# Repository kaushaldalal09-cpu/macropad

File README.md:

# macropad

This macropad will serve three purposes. One is to increase efficiency for my work by opening my most used apps with the click of a button. The second purpose is for playing video games. And the third feature I want is to have a built in game of tetris using the keys and oled display. My macro pad will include a knob (which will increase/decrease the volume) , a oled screen (to show the volume, or the tetris game depending on what mode I'm in), 12 keys, and RGB lights. 

All silkscreen artwork was created by me

BOM:
|Reference                                      |Qty|Value               |DNP|Exclude from BOM |Exclude from Board|Footprint                                                     |Datasheet                                                                 |
|-----------------------------------------------|---|--------------------|---|-----------------|------------------|--------------------------------------------------------------|--------------------------------------------------------------------------|
|C1                                             |1  |1.0uF               |   |                 |                  |Capacitor_THT:C_Axial_L5.1mm_D3.1mm_P15.00mm_Horizontal       |~                                                                         |
|D1,D2,D3,D4,D5,D6,D7,D8,D9                     |9  |1N4148              |   |                 |                  |Diode_THT:D_DO-35_SOD27_P7.62mm_Horizontal                    |https://assets.nexperia.com/documents/data-sheet/1N4148_1N4448.pdf        |
|D10,D11,D12,D13,D14,D15,D16,D17,D18,D19,D20,D21|12 |SK6812MINI          |   |                 |                  |LED_SMD:LED_SK6812MINI_PLCC4_3.5x3.5mm_P1.75mm                |https://cdn-shop.adafruit.com/product-files/2686/SK6812MINI_REV.01-1-2.pdf|
|H1,H2,H3,H4                                    |4  |MountingHole        |   |Excluded from BOM|                  |MountingHole:MountingHole_3.2mm_M3                            |~                                                                         |
|J1                                             |1  |Conn_01x04_Pin      |   |                 |                  |Connector_PinHeader_2.54mm:PinHeader_1x04_P2.54mm_Vertical    |~                                                                         |
|R1,R2                                          |2  |4.7K                |   |                 |                  |Resistor_THT:R_Axial_DIN0207_L6.3mm_D2.5mm_P10.16mm_Horizontal|~                                                                         |
|SW1,SW2,SW3,SW4,SW5,SW6,SW7,SW8                |8  |SW_Push             |   |                 |                  |Button_Switch_Keyboard:SW_Cherry_MX_1.00u_PCB                 |~                                                                         |
|SW9                                            |1  |RotaryEncoder_Switch|   |                 |                  |Rotary_Encoder:RotaryEncoder_Alps_EC11E-Switch_Vertical_H20mm |~                                                                         |
|U1                                             |1  |XIAO-RP2040-DIP     |   |                 |                  |OPL Lib:XIAO-RP2040-DIP                                       |                                                                          |

Resources used:

https://www.thingiverse.com/thing:6940808

https://github.com/ConstantinoSchillebeeckx/cherry-mx-switch/blob/master/switch.step

https://github.com/ConstantinoSchillebeeckx/cherry-mx-keycaps/blob/master/STEP/Cherry%20MX%20keycaps.step

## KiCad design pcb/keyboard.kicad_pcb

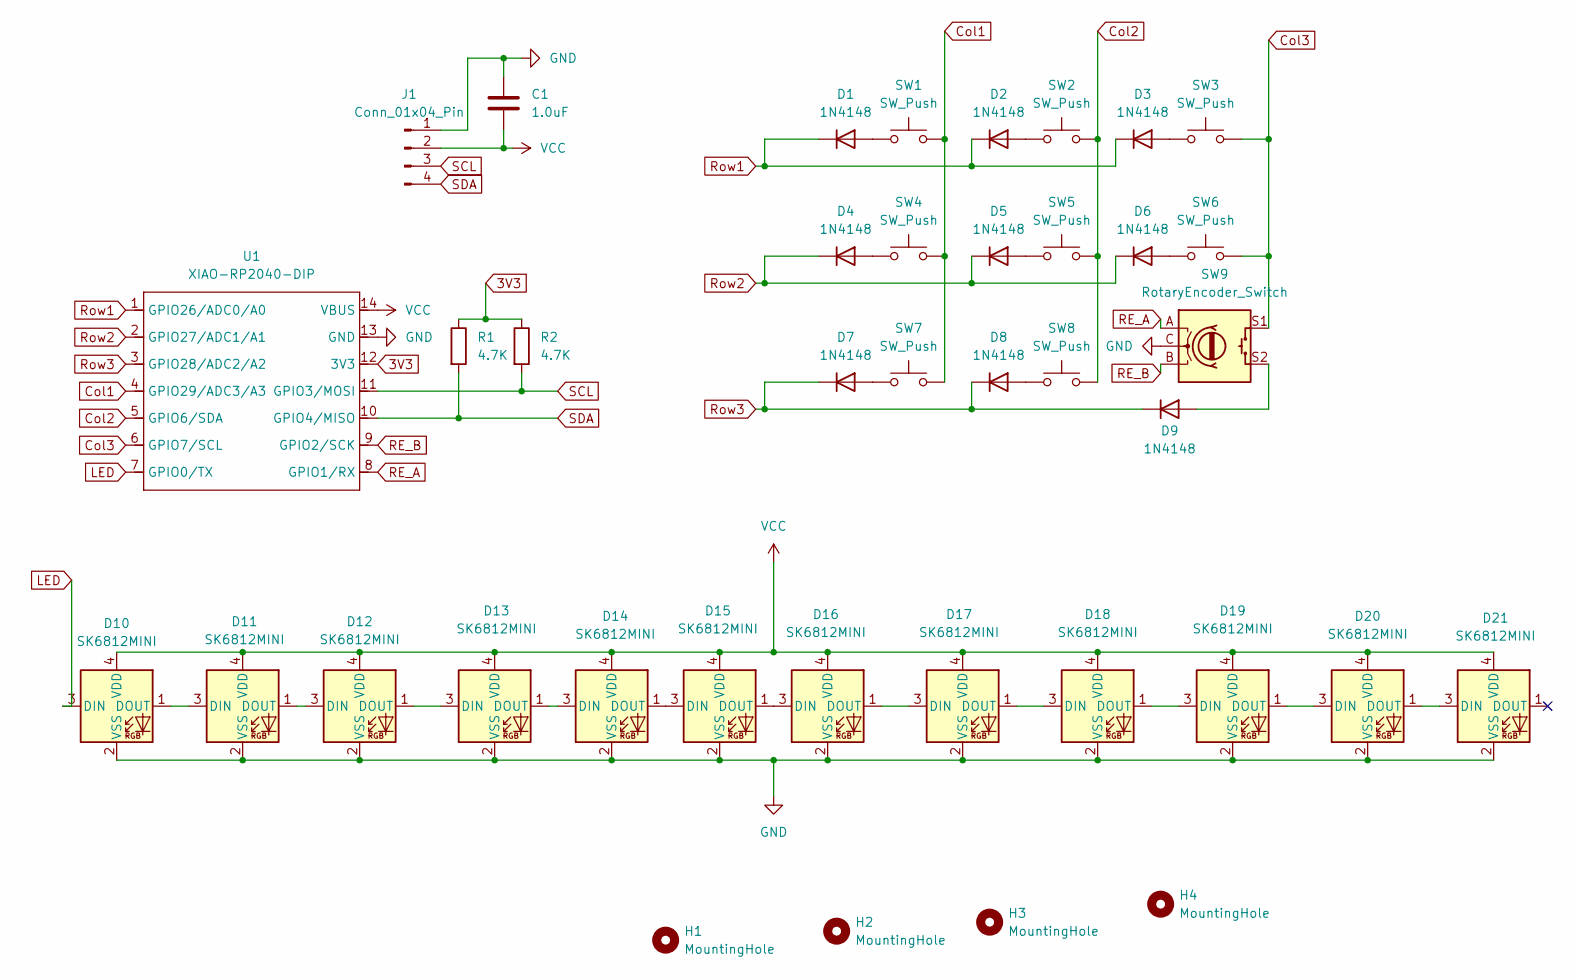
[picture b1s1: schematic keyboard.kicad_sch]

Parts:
C1: 1.0uF; C_Axial_L5.1mm_D3.1mm_P15.00mm_Horizontal
D1, D2, D3, D4, D5, D6, D7, D8, D9: 1N4148; D_DO-35_SOD27_P7.62mm_Horizontal
D10, D11, D12, D13, D14, D15, D16, D17, D18, D19, D20, D21: SK6812MINI; LED_SK6812MINI_PLCC4_3.5x3.5mm_P1.75mm
H1, H2, H3, H4: MountingHole; MountingHole_3.2mm_M3
J1: Conn_01x04_Pin; PinHeader_1x04_P2.54mm_Vertical
R1, R2: 4.7K; R_Axial_DIN0207_L6.3mm_D2.5mm_P10.16mm_Horizontal
SW1, SW2, SW3, SW4, SW5, SW6, SW7, SW8: SW_Push; SW_Cherry_MX_1.00u_PCB
SW9: RotaryEncoder_Switch; RotaryEncoder_Alps_EC11E-Switch_Vertical_H20mm
U1: XIAO-RP2040-DIP

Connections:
3V3: R1.1, R2.1, U1.12 (3V3)
Col1: SW1.2, SW4.2, SW7.2, U1.4 (GPIO29/ADC3/A3)
Col2: SW2.2, SW5.2, SW8.2, U1.5 (GPIO6/SDA)
Col3: SW3.2, SW6.2, SW9.S1, U1.6 (GPIO7/SCL)
GND: C1.1, D10.2 (VSS), D11.2 (VSS), D12.2 (VSS), D13.2 (VSS), D14.2 (VSS), D15.2 (VSS), D16.2 (VSS), D17.2 (VSS), D18.2 (VSS), D19.2 (VSS), D20.2 (VSS), D21.2 (VSS), J1.1, SW9.C, U1.13 (GND)
LED: D10.3 (DIN), U1.7 (GPIO0/TX)
unnamed: D1.2 (A), SW1.1
unnamed: D2.2 (A), SW2.1
unnamed: D3.2 (A), SW3.1
unnamed: D4.2 (A), SW4.1
unnamed: D5.2 (A), SW5.1
unnamed: D6.2 (A), SW6.1
unnamed: D7.2 (A), SW7.1
unnamed: D8.2 (A), SW8.1
unnamed: D9.2 (A), SW9.S2
unnamed: D10.1 (DOUT), D11.3 (DIN)
unnamed: D11.1 (DOUT), D12.3 (DIN)
unnamed: D12.1 (DOUT), D13.3 (DIN)
unnamed: D13.1 (DOUT), D14.3 (DIN)
unnamed: D14.1 (DOUT), D15.3 (DIN)
unnamed: D15.1 (DOUT), D16.3 (DIN)
unnamed: D16.1 (DOUT), D17.3 (DIN)
unnamed: D17.1 (DOUT), D18.3 (DIN)
unnamed: D18.1 (DOUT), D19.3 (DIN)
unnamed: D19.1 (DOUT), D20.3 (DIN)
unnamed: D20.1 (DOUT), D21.3 (DIN)
RE_A: SW9.A, U1.8 (GPIO1/RX)
RE_B: SW9.B, U1.9 (GPIO2/SCK)
Row1: D1.1 (K), D2.1 (K), D3.1 (K), U1.1 (GPIO26/ADC0/A0)
Row2: D4.1 (K), D5.1 (K), D6.1 (K), U1.2 (GPIO27/ADC1/A1)
Row3: D7.1 (K), D8.1 (K), D9.1 (K), U1.3 (GPIO28/ADC2/A2)
SCL: J1.3, R2.2, U1.11 (GPIO3/MOSI)
SDA: J1.4, R1.2, U1.10 (GPIO4/MISO)
VCC: C1.2, D10.4 (VDD), D11.4 (VDD), D12.4 (VDD), D13.4 (VDD), D14.4 (VDD), D15.4 (VDD), D16.4 (VDD), D17.4 (VDD), D18.4 (VDD), D19.4 (VDD), D20.4 (VDD), D21.4 (VDD), J1.2, U1.14 (VBUS)

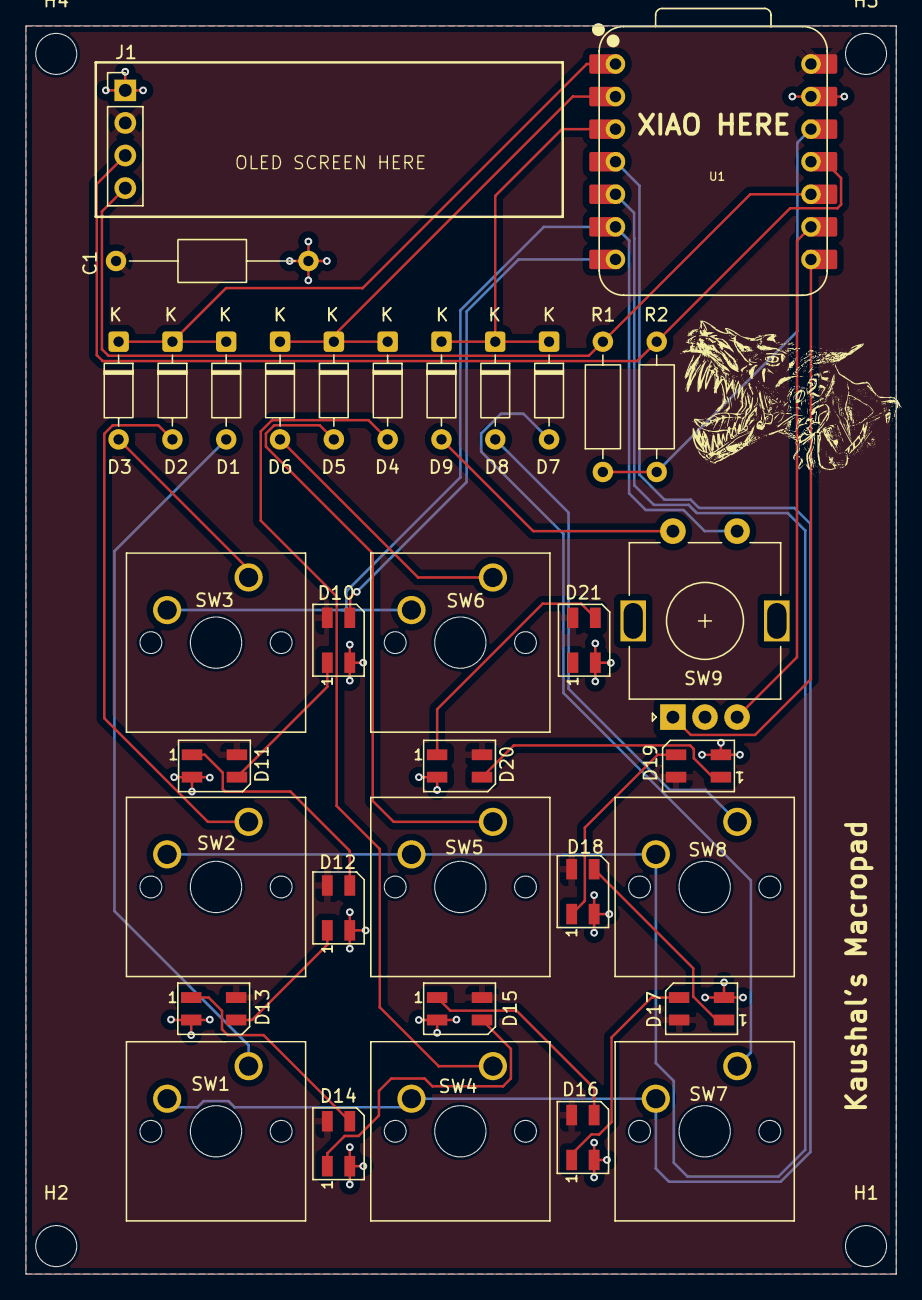
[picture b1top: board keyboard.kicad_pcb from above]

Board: 2 copper layers, 67.9 x 97.3 mm, 39 parts (0 on the bottom side), 34 nets.

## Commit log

2025-12-31 added design files
2025-12-31 added images
2026-01-05 new pcb image
